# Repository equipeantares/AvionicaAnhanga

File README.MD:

# Base de Acionamento

## Introdução 

### Motivação

A equipe Antares de espaçomodelismo da Unicamp tem como um de seus projetos desenvolvidos o foguete Aurora. Trata-se de um foguete de propulsão sólida com apogeu esperado de 3km. Como parte dos requisitos necessários para ter sucesso na missão, o foguete precisa de um sistema de aviônica que será responsável por coletar dados e tomar decisões previamente programadas durante o voo. Com o objetivo de monitorar o estado do foguete antes, durante e depois do lançamento, é necessário ter um sistema em solo que seja capaz de receber os dados coletados pela aviônica, permitindo que os presentes tenham informações em tempo real. Além disso, esse sistema deve permitir que o acionador do motor seja ligado de forma segura durante o lançamento, não expondo pessoas a riscos.

### Objetivo

Sendo assim, o objetivo deste projeto é desenvolver um sistema de controle de base para o foguete, o qual deve ser capaz de iniciar o lançamento de forma segura e robusta e capaz de receber e apresentar dados da telemetria do voo colhidos pela aviônica.

### Soluções comerciais

Pelo fato de o sistema precisar ser personalizado, se ajustando ao sistema presente no foguete e aos demais requisitos específicos do projeto, não existem alternativas comerciais que cumpram integralmente o objetivo.

## Especificação
    - Microcontrolador: o dispositivo deverá ser capaz de fazer processamentos lógicos, sendo assim necessário um microcontrolador. Por motivos de acessibilidade e familiaridade, será utilizada a plataforma Arduino no MCU ESP-8266 12F.

    - Comunicação e dados: com o objetivo de receber dados de telemetria do foguete, o dispositivo deverá ter um sistema transceptor, que será implementado por um módulo LoRA E32-915T20D.

    - Interface: como interface, o dispositivo contará com pinos auxiliares para monitoramento do funcionamento da placa e pinos de seleção de função para alimentação e modo de acionamento da ignição, sendo a seleção feita por meio de jumpers.

    - Ignição: deverá suportar dois modos de acionamento do circuito ignitor: por sinal elétrico e por comando remoto. O modo será escolhido via inserção manual de jumpers antes do lançamento.

    - Alimentação: o sistema deverá ter interface de alimentação, podendo operar com a alimentação interna de 3V3 ou alimentação externa de 5V.

## Diagrama

## Pinagem

### Pinout conector Screw bateria 18650

Pino | Sinal
-----|------
1  | VBat
2  | GND

### Pinout conector Screw do Acionamento

Pino | Sinal
-----|------
  1  | NiCr_ISO
  2  | GND_ISO

### Pinout conector Screw Alimentação externa

Pino | Sinal
-----|------
  1  | VExt
  2  | GND

### Pinout conector GPIO aux

Pino | Sinal
-----|------
  1  | DIO1
  2  | DIO2
  3  | 3V3
  4  | GND

### Pinout conector LoRA aux

Pino | Sinal
-----|------
  1  | OutputLora
  2  | InputLora
  3  | 3V3
  4  | GND

### Pinout conector I2C aux

Pino | Sinal
-----|------
  1  | SCL_SLAVE
  2  | SDA_SLAVE
  3  | 3V3
  4  | GND

### Pinout conector SPI aux

Pino | Sinal
-----|------
  1  | MOSI
  2  | CS
  3  | MISO
  4  | SCLK
  5  | GND

### Pinout conector de seleção alimentação LoRA

Pino | Sinal
-----|------
  1  | 3V3
  2  | VLora
  3  | VExt

### Pinout conector Transistor PNP acionamento (interno)

Pino | Sinal
-----|------
  1  | Emissor
  2  | Coletor

### Pinout conector Optoacoplador acionamento (externo)

Pino | Sinal
-----|------
  1  | Coletor
  2  | Emissor

## Testes

    A fim de garantir que o sistema seja seguro e que tudo funcione como esperado, é necessário realizar testes controlados de cada parte do sistema, tentando antecipar possíveis falhas que possam ocorrer. 
    Como o sistema de ignição não pode ter acionamento indesejado, devem ocorrer testes em ambientes adversos, como, por exemplo, com componentes desconectados, e o resultado esperado é que o sistema não ative em nenhuma dessas situações.

## Relatório de funcionamento
	Durante o desenvolvimento do projeto foram encotradas algumas falhas que devem ser corrigidas na próxima versão da aviônica. A primeira delas é referente a pinagem do SPI, que estão incorretamente conectadas nos pinos de flash do microcontrolador, de forma que o módulo do cartão SD não funcione como desejado.
	 A segunda falha é o pino do buzzer, que é um pino que é usado para o boot da placa. Isso faz com que o buzzer fique ativado por todo o tempo durante o upload do código, tornando o processo de desenvolvimento do projeto um tanto irritante. Além disso, ocorreram erros por usar esse pino como saída no código, então, para uma próxima atualização do projeto, seria interessante utilizar uma outra GPIO diferente da 9 para operar este dispositivo.
	 Uma outra melhoria que pode ser feita no projeto é repensar o sitema da ignição da recuperação. A utilização de um dispositivo eletromecânico como o relê faz com que possa haver um acionamento indesejado devido à aceleração e movimentação do foguete. Sendo assim, seria mais seguro utilizar um circuito de acionamento digital, utilizando MOSFETs. Além disso, seria interessante implementar um circuito que fosse capaz de identificar a presença ou não do ignitor. Algo assim foi desenvolvido anteriormente pela equipe e o projeto pode ser acessado nas documentações antigas.

Relatório desenvolvido por: Gustavo S. Reis em 01/12/2022

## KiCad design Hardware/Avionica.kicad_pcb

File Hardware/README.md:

# Projeto de Aviônica Icaro_II

Última atualização feita por Gustavo Reis (gustavosr8@gmail.com)

## Introdução 

### Motivação

A equipe Antares de espaçomodelismo da Unicamp tem como um de seus projetos desenvolvidos o foguete Anhangá. Trata-se de um foguete de propulsão sólida com apogeu esperado de 1km. Como parte dos requisitos necessários para ter sucesso na missão, o foguete precisa de um sistema de aviônica que será responsável por coletar dados e tomar decisões previamente programadas durante o voo. 

### Objetivo

Sendo assim, o objetivo deste projeto é desenvolver um sistema embarcado para o foguete, capaz de captar dados referentes ao voo, armazenar esses dados de forma segura e tomar decisões baseadas nas leituras feitas.

### Soluções comerciais

Pelo fato de o sistema precisar ser personalizado, se ajustando ao sistema presente no foguete e aos demais requisitos específicos do projeto, não existem alternativas comerciais que cumpram integralmente o objetivo.

## Especificação
    - Microcontrolador: o dispositivo deverá ser capaz de fazer processamentos lógicos, sendo assim necessário um microcontrolador. Por motivos de acessibilidade e familiaridade, será utilizada a plataforma Arduino no MCU ESP-8266 12F.

    - Dados: com o objetivo de receber dados de telemetria do foguete e armazená-los de forma segura, será utilizado um módulo para cartão micro SD e um cartão de 16GB.

    - Interface: como interface, o dispositivo contará com pinos auxiliares para monitoramento do funcionamento da placa e pinos de seleção de função para alimentação e modo de acionamento da ignição, sendo a seleção feita por meio de jumpers.

    - Ignição: deverá suportar dois modos de acionamento do circuito ignitor: por sinal elétrico e por comando remoto. O modo será escolhido via inserção manual de jumpers antes do lançamento.

    - Alimentação: o sistema deverá ter interface de alimentação, podendo operar com a alimentação interna de 3V3 ou alimentação externa de 5V.

## Testes

    A fim de garantir que o sistema seja seguro e que tudo funcione como esperado, é necessário realizar testes controlados de cada parte do sistema, tentando antecipar possíveis falhas que possam ocorrer. 
    Como o sistema de ignição não pode ter acionamento indesejado, devem ocorrer testes em ambientes adversos, como, por exemplo, com componentes desconectados, e o resultado esperado é que o sistema não ative em nenhuma dessas situações.

## Considerações e melhorias futuras

O sistema foi implementado e integrado no foguete Aurora I, para a LASC 2022. A captura de dados se mostrou muito robusta e o sistema de filtragem destes se demonstrou eficiente. A alimentação também teve um bom desempenho (foram utilizadas 2 baterias 18650 para iginição e uma do mesmo tipo para alimentação da placa) e podem até ser estudadas opções de desempenho energético inferior, porém com menor massa. Como pontos negativos para futuras melhorias cabe destacar a pinagem do buzzer, que era em um pino que se ativava sempre que o microcontrolador bootava, tornando o processo de desenvolvimento e debug um tanto desagradável dado o som estridente do dispositivo. O uso de um relay como acionador da ignição também é um ponto negativo do projeto, já que é um dispositivo eletro-mecânico, e, em presença de muito movimento e alta aceleração, como acontece no foguete, pode ocorrer um acionamento indesejado, causando a falha da missão. Uma solução para isso pode ser implementar um acionamento digital via MOSFET. Um último ponto a ser melhorado é a questão da redundância para garantir o sucesso da missão. Esse problema não tem tem uma solução trivial, e deve ser estudado.

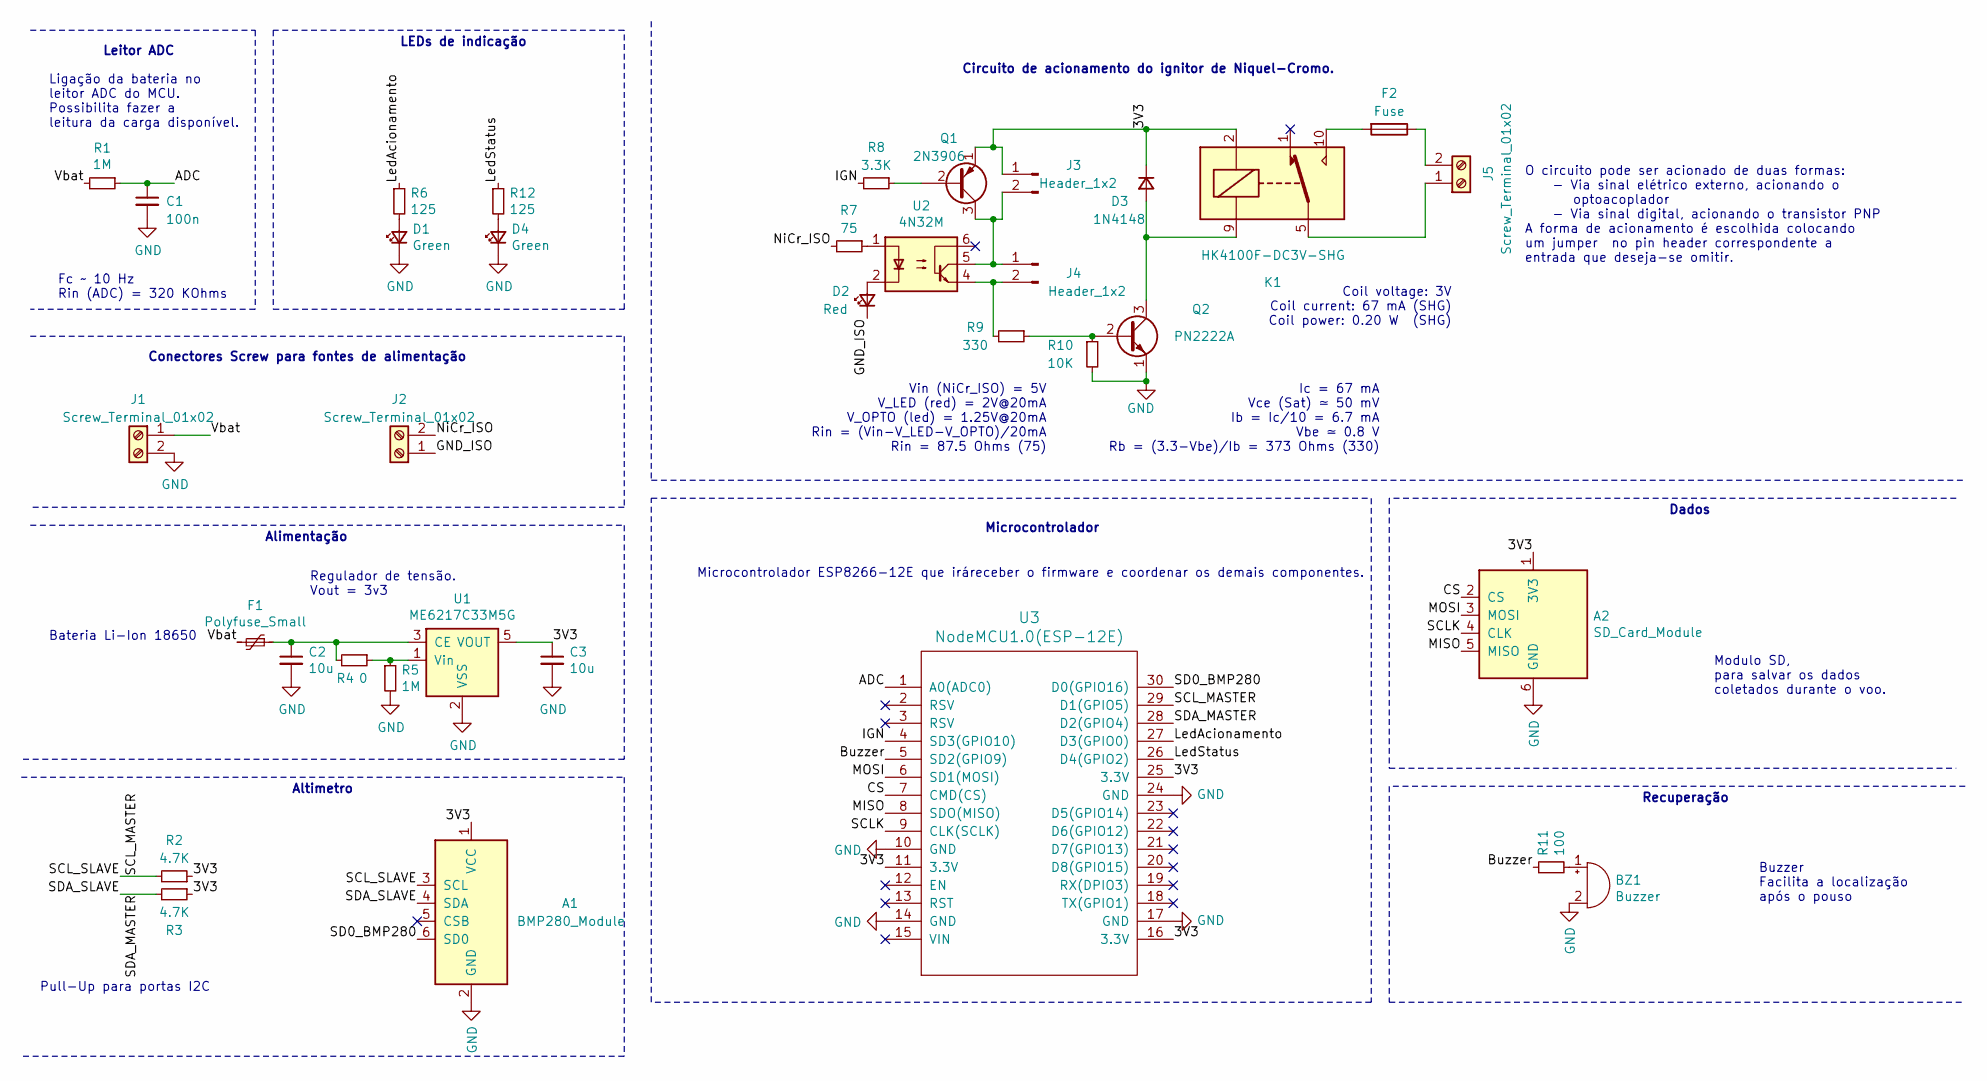
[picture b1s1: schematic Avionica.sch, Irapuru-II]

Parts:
A1: BMP280_Module
A2: SD_Card_Module
BZ1: Buzzer; Buzzer_12x9.5RM7.6
C1: 100n; C_0805_2012Metric
C2, C3: 10u; C_0805_2012Metric
D1, D4: Green; LED_D3.0mm
D2: Red; LED_D3.0mm
D3: 1N4148; D_SOD-123
F1: Polyfuse_Small; Fuse_1206_3216Metric_Castellated
F2: Fuse; Fuseholder_Cylinder-5x20mm_Stelvio-Kontek_PTF78_Horizontal_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
J1, J2, J5: Screw_Terminal_01x02; TerminalBlock_Phoenix_MKDS-1,5-2_1x02_P5.00mm_Horizontal
J3, J4: Header_1x2; Molex_KK-254_AE-6410-02A_1x02_P2.54mm_Vertical
K1: HK4100F-DC3V-SHG; Relay_SPDT_HJR-4102
Q1: 2N3906; TO-92_Inline
Q2: PN2222A; TO-92_Inline
R1, R5: 1M; R_0805_2012Metric
R2, R3: 4.7K; R_0805_2012Metric
R4: 0; R_0805_2012Metric
R6, R12: 125; R_0805_2012Metric
R7: 75; R_0805_2012Metric
R8: 3.3K; R_0805_2012Metric
R9: 330; R_0805_2012Metric
R10: 10K; R_0805_2012Metric
R11: 100; R_0805_2012Metric
U1: ME6217C33M5G; SOT-23-5
U2: 4N32M; DIP-6_W7.62mm
U3: NodeMCU1.0(ESP-12E); ESP12F-Devkit-V3

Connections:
/3V3: A1.1 (VCC), A2.1 (3V3), C3.1, D3.1 (K), J3.1, K1.2, Q1.1 (E), R2.1, R3.1, U1.5 (VOUT), U3.11 (3.3V), U3.16 (3.3V), U3.25 (3.3V)
/ADC: C1.1, R1.1, U3.1 (A0(ADC0))
/Buzzer: R11.1, U3.5 (SD2(GPIO9))
/CS: A2.2 (CS), U3.7 (CMD(CS))
/GND_ISO: D2.1 (K), J2.1
/IGN: R8.2, U3.4 (SD3(GPIO10))
/LedAcionamento: R6.1, U3.27 (D3(GPIO0))
/LedStatus: R12.1, U3.26 (D4(GPIO2))
/MISO: A2.5 (MISO), U3.8 (SDO(MISO))
/MOSI: A2.3 (MOSI), U3.6 (SD1(MOSI))
/NiCr_ISO: J2.2, R7.2
/SCLK: A2.4 (CLK), U3.9 (CLK(SCLK))
/SCL_MASTER: A1.3 (SCL), R2.2, U3.29 (D1(GPIO5))
/SD0_BMP280: A1.6 (SD0), U3.30 (D0(GPIO16))
/SDA_MASTER: A1.4 (SDA), R3.2, U3.28 (D2(GPIO4))
/Vbat: F1.2, J1.1, R1.2
GND: A1.2 (GND), A2.6 (GND), BZ1.2 (+), C1.2, C2.2, C3.2, D1.1 (K), D4.1 (K), J1.2, Q2.1 (E), R5.2, R10.2, U1.2 (VSS), U3.10 (GND), U3.14 (GND), U3.17 (GND), U3.24 (GND)
unnamed: BZ1.1 (-), R11.2
unnamed: C2.1, F1.1, R4.2, U1.3 (CE)
unnamed: D1.2 (A), R6.2
unnamed: D2.2 (A), U2.2
unnamed: D3.2 (A), K1.9, Q2.3 (C)
unnamed: D4.2 (A), R12.2
unnamed: F2.1, J5.2
unnamed: F2.2, K1.10
unnamed: J3.2, J4.1, Q1.3 (C), U2.5
unnamed: J4.2, R9.2, U2.4
unnamed: J5.1, K1.5, K1.6
unnamed: Q1.2 (B), R8.1
unnamed: Q2.2 (B), R9.1, R10.1
unnamed: R4.1, R5.1, U1.1 (Vin)
unnamed: R7.1, U2.1

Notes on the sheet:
Coil voltage: 3V Coil current: 67 mA (SHG) Coil power: 0.20 W (SHG)
Fc ~~ 10 Hz Rin (ADC) = 320 KOhms
Conectores Screw para fontes de alimentação
LEDs de indicação
Ligação da bateria no leitor ADC do MCU. Possibilita fazer a leitura da carga disponível.
Microcontrolador ESP8266-12E que iráreceber o firmware e coordenar os demais componentes.
O circuito pode ser acionado de duas formas: - Via sinal elétrico externo, acionando o optoacoplador - Via sinal digital, acionando o transistor PNP A forma de acionamento é escolhida colocando um jumper no pin header correspondente a entrada que deseja-se omitir.
Microcontrolador
Dados
Alimentação
Leitor ADC
Circuito de acionamento do ignitor de Niquel-Cromo.
Ic = 67 mA Vce (Sat) ≃ 50 mV Ib = Ic/10 = 6.7 mA Vbe ≃ 0.8 V Rb = (3.3-Vbe)/Ib = 373 Ohms (330)
Vin (NiCr_ISO) = 5V V_LED (red) = 2V@20mA V_OPTO (led) = 1.25V@20mA Rin = (Vin-V_LED-V_OPTO)/20mA Rin = 87.5 Ohms (75)
Recuperação
Altimetro
Pull-Up para portas I2C
Modulo SD, para salvar os dados coletados durante o voo.
Buzzer Facilita a localização após o pouso
Regulador de tensão. Vout = 3v3
Bateria Li-Ion 18650

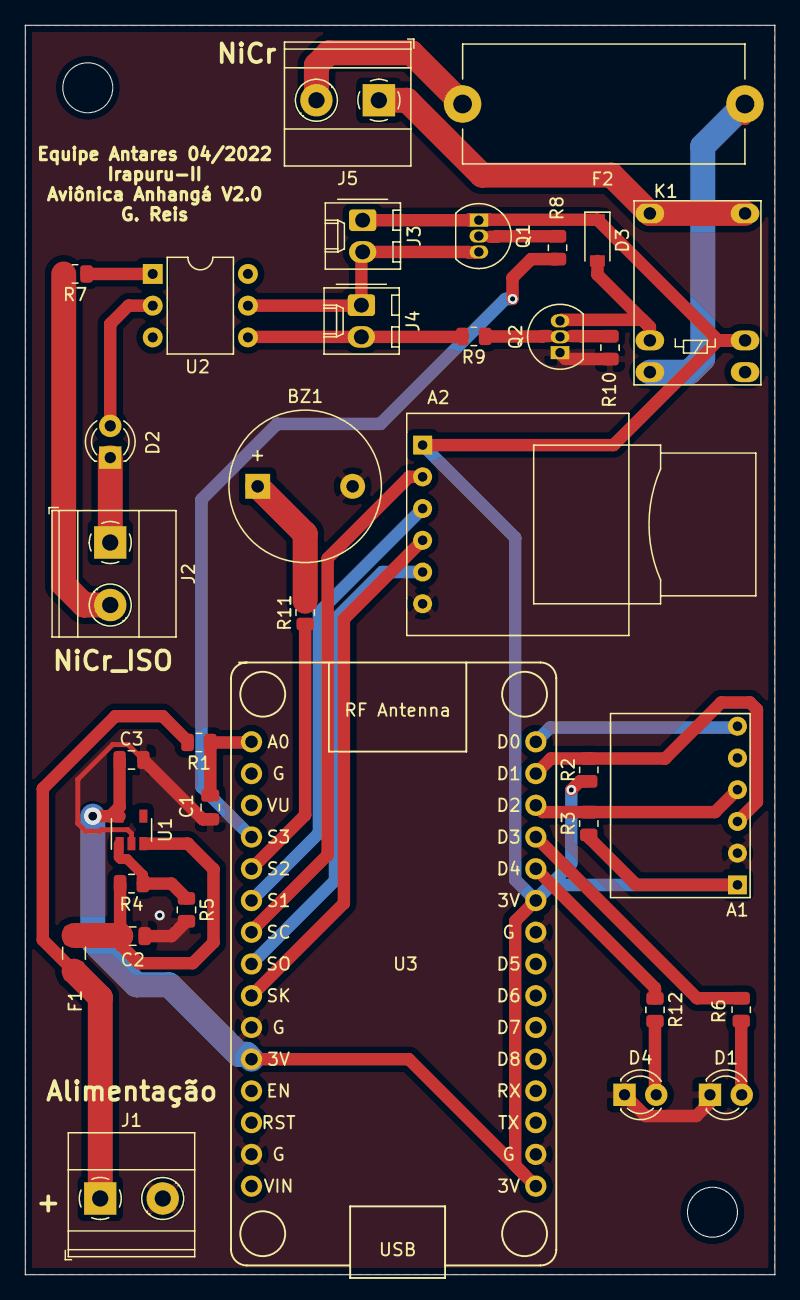
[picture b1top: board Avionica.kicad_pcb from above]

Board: 2 copper layers, 60.0 x 100.0 mm, 35 parts (0 on the bottom side), 32 nets.

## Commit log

2019-10-23 Primeiro commit
2019-10-24 Codigo para teste do BMP280 e SD
2019-10-26 Codigo do cansat
2019-11-05 Código com 2 BMP's e salvando no SD
2019-11-05 Set sample bmp2
2019-11-22 Added Timer Interruption + Initialization + State Machine on loop().
2019-11-23 classes
2019-11-26 Finished merging and tests on BMPs and classes - OK
2019-11-26 After CEPETRO test - Working code
2019-11-30 Code cleanup + comments
2019-12-03 Filter implementation and most conditions for state machine - prototype
2019-12-03 Added code for end of propulsion condition
2019-12-04 Ejection test - filter and ignition corrected
2019-12-04 Ejection test - Ready for new board
2019-12-05 Elevator test - Code working
2019-12-05 Code ready for flight - 05/12/19
2021-05-14 Added TODO for velocity decision considerations
2022-10-06 projeto de hardware desenvolvido para a placa Irapuru II
2022-11-30 firmware para uso no ESP8266
2022-12-01 adiciona documentação
